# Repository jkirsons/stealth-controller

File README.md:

# Stealth Controller
A Field Oriented Control Brushless DC Motor Controller.

With 8A driver, Magnetic Sensor, Microcontroller, Two-Wire Automotive Interface

---
BOM

Ref | Qnty | Value | Size | LCSC #
--- | --- | --- | --- | --- 
C3, C21, C22, C23, C24, C25, C26, |7|22uF 25v|0805|[C45783](https://lcsc.com/product-detail/Multilayer-Ceramic-Capacitors-MLCC-SMD-SMT_Samsung-Electro-Mechanics-CL21A226MAQNNNE_C45783.html)
C1, C15, C16, |3|22uF 10v|0603|[C86295](https://lcsc.com/product-detail/Multilayer-Ceramic-Capacitors-MLCC-SMD-SMT_Samsung-Electro-Mechanics-CL10A226MP8NUNE_C86295.html)
C9, C18, C20, |3|10uF 10v|0603|[C19702](https://lcsc.com/product-detail/Multilayer-Ceramic-Capacitors-MLCC-SMD-SMT_Samsung-Electro-Mechanics-CL10A106KP8NNNC_C19702.html)
C11, |1|2.2uF 50v|0805|[C337444](https://lcsc.com/product-detail/Others_Taiyo-Yuden-UMK212ABJ225KG-T_C337444.html)
C4, C6, C10, C13, |4|1uF 16v|0603|[C318643](https://lcsc.com/product-detail/Multilayer-Ceramic-Capacitors-MLCC-SMD-SMT_Samsung-Electro-Mechanics-CL10A105KO5LNNC_C318643.html)
C2, C7, C8, C12, C14, C17, C19, |7|100nF 50v|0603|[C490602](https://lcsc.com/product-detail/Multilayer-Ceramic-Capacitors-MLCC-SMD-SMT_KEMET-C0603C104J5RAC_C490602.html)
C5, |1|10nF 50v|0603|[C128615](https://lcsc.com/product-detail/Multilayer-Ceramic-Capacitors-MLCC-SMD-SMT_Walsin-Tech-Corp-0603B103J500CT_C128615.html)
L1, |1|15uH|1210|[C478845](https://lcsc.com/product-detail/Inductors-SMD_Taiyo-Yuden-BRL3225T150K_C478845.html)
R1, |1|22|0603|[C269708](https://lcsc.com/product-detail/Chip-Resistor-Surface-Mount_TyoHM-RMC0603221-N_C269708.html)
R2|1|5.1k|0603|[C103696](https://lcsc.com/product-detail/Chip-Resistor-Surface-Mount_RALEC-RTT03512JTP_C103696.html)
R3, R4, |2|10K|0603|[C328335](https://lcsc.com/product-detail/Chip-Resistor-Surface-Mount_Resistor-Today-AECR0603F10K0K9_C328335.html)
R5, |1|120|0603|[C22787](https://lcsc.com/product-detail/Chip-Resistor-Surface-Mount_UNI-ROYAL-Uniroyal-Elec-0603WAF1200T5E_C22787.html)
IC1, |1|ESP32-PICO-V3|ESP32-PICO-V3|[C967022](https://lcsc.com/product-detail/RF-Transceiver-ICs_Espressif-Systems-ESP32-PICO-V3_C967022.html)
IC2, |1|LMR36506|LMR36506|[TI](https://www.ti.com/store/ti/en/p/product/?p=LMR36506R3RPER)
IC3, |1|MA702GQ-P|MA702GQ-P|[Mouser](https://www.mouser.ch/ProductDetail/Monolithic-Power-Systems-MPS/MA702GQ-P?qs=%2Fha2pyFadugcckvyIxaK%2FPg3fxrEo4S43%2FImNSAiLmAbp7VlBKN7pA%3D%3D)
IC4, |1|SN65HVD230QDRG4|SN65HVD230QDRG4|[C16468](https://lcsc.com/product-detail/CAN-ICs_Texas-Instruments-SN65HVD230QDR_C16468.html)
U1, |1|DRV8316R|DRV8316R|[TI](https://www.ti.com/product/DRV8316?keyMatch=DRV8316&tisearch=search-everything&usecase=GPN#order-quality)
Reset1, Boot1, |2|SW_Push_Dual|XKB Connectivity TS-1177-B-B-B|[C561510](https://lcsc.com/product-detail/Tactile-Switches_XKB-Connectivity-TS-1177-B-B-B_C561510.html)
UART1, TWAI1, TWAI2, |3|UART/TWAI|S3B-ZR-SM4A-TF|[C158001](https://lcsc.com/product-detail/Wire-To-Board-Wire-To-Wire-Connector_JST-Sales-America-B3B-ZR-LF-SN_C158001.html)
J1, |1|XT30PB|XT30PB|[C428721](https://lcsc.com/product-detail/Power-Connectors_Changzhou-Amass-Elec-XT30UPB-M_C428721.html)

---

Links:
[Simple FOC](https://simplefoc.com/)

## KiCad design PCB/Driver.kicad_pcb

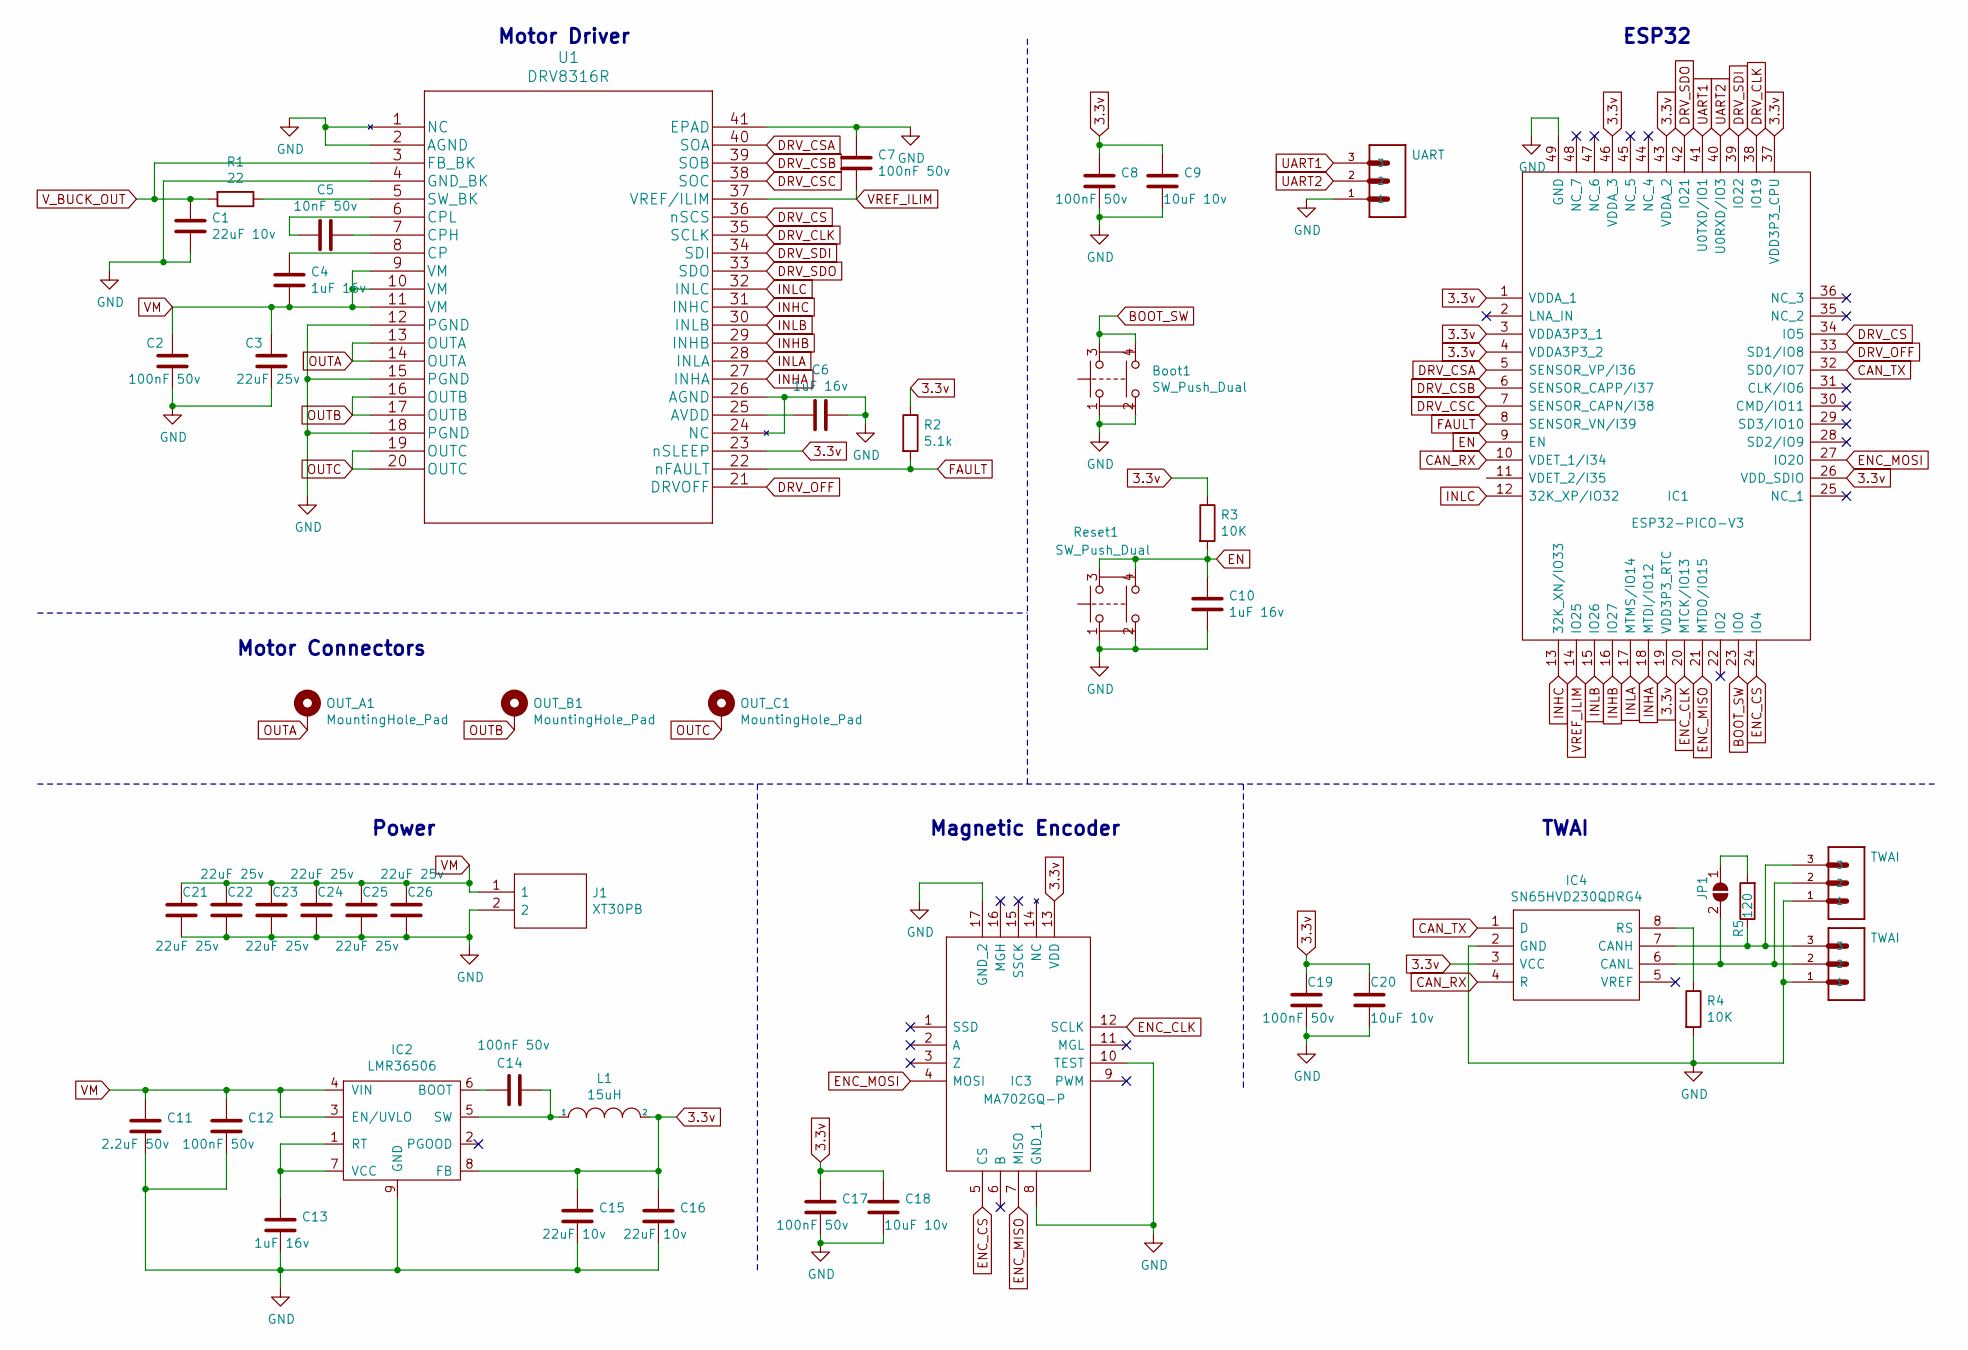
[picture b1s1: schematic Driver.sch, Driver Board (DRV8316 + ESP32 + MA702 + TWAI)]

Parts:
Boot1: SW_Push_Dual; XKB_Connectivity_TS-1177-B-B-B
C1, C15, C16: 22uF 10v; C_0603_1608Metric
C2, C7, C8, C12, C14, C17, C19: 100nF 50v; C_0603_1608Metric
C3, C21, C22, C23, C24, C25, C26: 22uF 25v; C_0805_2012Metric
C4, C6, C10, C13: 1uF 16v; C_0603_1608Metric
C5: 10nF 50v; C_0603_1608Metric
C9, C18, C20: 10uF 10v; C_0603_1608Metric
C11: 2.2uF 50v; C_0805_2012Metric
IC1: ESP32-PICO-V3; ESP32PICOV3; Manufacturer_Part_Number ESP32-PICO-V3; Mouser Part Number 356-ESP32-PICO-V3
IC2: LMR36506
IC3: MA702GQ-P; MA702; Manufacturer_Part_Number MA702GQ-P; Mouser Part Number 946-MA702GQ-P
IC4: SN65HVD230QDRG4; SN65HVD230QDR; Manufacturer_Part_Number SN65HVD230QDRG4; Mouser Part Number 595-SN65HVD230QDRG4
J1: XT30PB; Manufacturer_Part_Number XT30PB
JP1: SolderJumper_2_Open; SolderJumper-2_P1.3mm_Open_RoundedPad1.0x1.5mm
L1: 15uH; L_1210_3225Metric; MPN NLCV32T-470K-PF; LCSC C83083
OUT_A1: MountingHole_Pad; Motor_Wire_Solder_Pad
OUT_B1: MountingHole_Pad; Motor_Wire_Solder_Pad
OUT_C1: MountingHole_Pad; Motor_Wire_Solder_Pad
R1: 22; R_0603_1608Metric
R2: 5.1k; R_0603_1608Metric
R3, R4: 10K; R_0603_1608Metric
R5: 120; R_0603_1608Metric
Reset1: SW_Push_Dual; XKB_Connectivity_TS-1177-B-B-B
TWAI1, TWAI2: TWAI; SHDR3W50P0X150
U1: DRV8316R; DRV8316
UART1: UART; SHDR3W50P0X150

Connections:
3.3v: C8.1, C9.1, C15.1, C16.1, C17.1, C18.1, C19.1, C20.1, IC1.1 (VDDA_1), IC1.3 (VDDA3P3_1), IC1.4 (VDDA3P3_2), IC1.19 (VDD3P3_RTC), IC1.26 (VDD_SDIO), IC1.37 (VDD3P3_CPU), IC1.43 (VDDA_2), IC1.46 (VDDA_3), IC2.8 (FB), IC3.13 (VDD), IC4.3 (VCC), L1.2, R2.1, R3.1, U1.23 (nSLEEP)
BOOT_SW: Boot1.3, Boot1.4, IC1.23 (IO0)
CAN_RX: IC1.10 (VDET_1/I34), IC4.4 (R)
CAN_TX: IC1.32 (SD0/IO7), IC4.1 (D)
DRV_CLK: IC1.38 (IO19), U1.35 (SCLK)
DRV_CS: IC1.34 (IO5), U1.36 (nSCS)
DRV_CSA: IC1.5 (SENSOR_VP/I36), U1.40 (SOA)
DRV_CSB: IC1.6 (SENSOR_CAPP/I37), U1.39 (SOB)
DRV_CSC: IC1.7 (SENSOR_CAPN/I38), U1.38 (SOC)
DRV_OFF: IC1.33 (SD1/IO8), U1.21 (DRVOFF)
DRV_SDI: IC1.39 (IO22), U1.34 (SDI)
DRV_SDO: IC1.42 (IO21), U1.33 (SDO)
EN: C10.1, IC1.9 (EN), R3.2, Reset1.3, Reset1.4
ENC_CLK: IC1.20 (MTCK/IO13), IC3.12 (SCLK)
ENC_CS: IC1.24 (IO4), IC3.5 (CS)
ENC_MISO: IC1.21 (MTDO/IO15), IC3.7 (MISO)
ENC_MOSI: IC1.27 (IO20), IC3.4 (MOSI)
FAULT: IC1.8 (SENSOR_VN/I39), R2.2, U1.22 (nFAULT)
GND: Boot1.1, Boot1.2, C1.2, C2.2, C3.2, C6.1, C7.1, C8.2, C9.2, C10.2, C11.2, C12.2, C13.2, C15.2, C16.2, C17.2, C18.2, C19.2, C20.2, C21.2, C22.2, C23.2, C24.2, C25.2, C26.2, IC1.49 (GND), IC2.9 (GND), IC3.8 (GND_1), IC3.10 (TEST), IC3.17 (GND_2), IC4.2 (GND), J1.2, R4.2, Reset1.1, Reset1.2, TWAI1.1, TWAI2.1, U1.1 (NC), U1.2 (AGND), U1.4 (GND_BK), U1.12 (PGND), U1.15 (PGND), U1.18 (PGND), U1.24 (NC), U1.26 (AGND), U1.41 (EPAD), UART1.1; also elsewhere on the board
INHA: IC1.18 (MTDI/IO12), U1.27 (INHA)
INHB: IC1.16 (IO27), U1.29 (INHB)
INHC: IC1.13 (32K_XN/IO33), U1.31 (INHC)
INLA: IC1.17 (MTMS/IO14), U1.28 (INLA)
INLB: IC1.15 (IO26), U1.30 (INLB)
INLC: IC1.12 (32K_XP/IO32), U1.32 (INLC)
unnamed: C4.1, U1.8 (CP)
unnamed: C5.1, U1.7 (CPH)
unnamed: C5.2, U1.6 (CPL)
unnamed: C6.2, U1.25 (AVDD)
unnamed: C13.1, IC2.1 (RT), IC2.7 (VCC)
unnamed: C14.1, IC2.6 (BOOT)
unnamed: C14.2, IC2.5 (SW), L1.1
unnamed 32: IC4.6 (CANL), JP1.2 (B), TWAI1.2, TWAI2.2; also elsewhere on the board
unnamed 33: IC4.7 (CANH), R5.1, TWAI1.3, TWAI2.3; also elsewhere on the board
unnamed: IC4.8 (RS), R4.1
unnamed: JP1.1 (A), R5.2
unnamed: R1.1, U1.5 (SW_BK)
OUTA: OUT_A1.1, U1.13 (OUTA), U1.14 (OUTA)
OUTB: OUT_B1.1, U1.16 (OUTB), U1.17 (OUTB)
OUTC: OUT_C1.1, U1.19 (OUTC), U1.20 (OUTC)
UART1: IC1.41 (U0TXD/IO1), UART1.3
UART2: IC1.40 (U0RXD/IO3), UART1.2
VM: C2.1, C3.1, C4.2, C11.1, C12.1, C21.1, C22.1, C23.1, C24.1, C25.1, C26.1, IC2.3 (EN/UVLO), IC2.4 (VIN), J1.1, U1.9 (VM), U1.10 (VM), U1.11 (VM)
VREF_ILIM: C7.2, IC1.14 (IO25), U1.37 (VREF/ILIM)
V_BUCK_OUT: C1.1, R1.2, U1.3 (FB_BK)

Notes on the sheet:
Motor Driver
Motor Connectors
ESP32
Magnetic Encoder
TWAI
Power

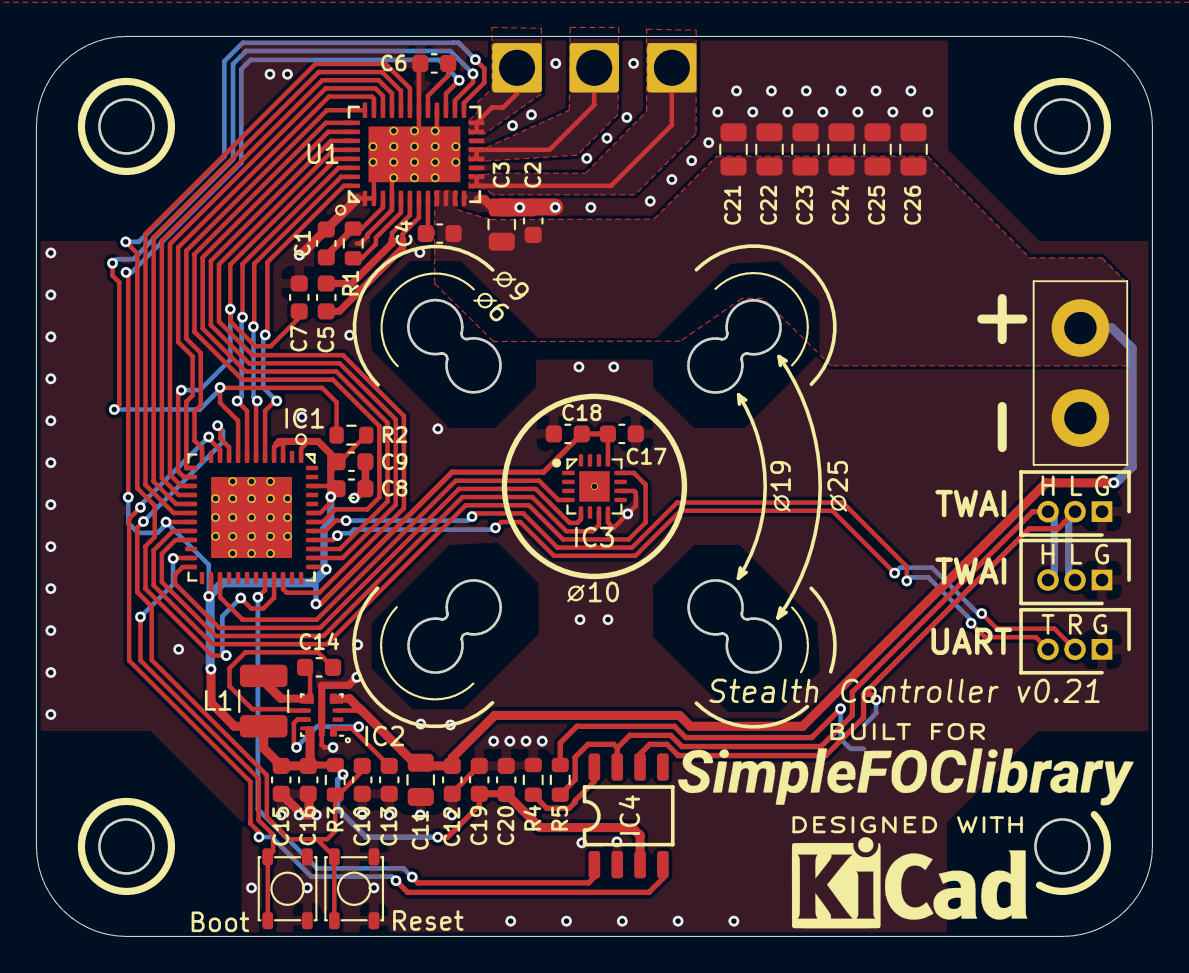
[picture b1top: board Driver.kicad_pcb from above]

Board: 2 copper layers, 62.0 x 50.0 mm, 47 parts (1 on the bottom side), 45 nets.

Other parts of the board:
CAN1, CAN2: CAN; SHDR3W50P0X150

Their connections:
GND: CAN1.1, CAN2.1; also elsewhere on the board
unnamed 32: CAN1.2, CAN2.2; also elsewhere on the board
unnamed 33: CAN1.3, CAN2.3; also elsewhere on the board

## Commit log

2021-05-02 add image
2021-05-02 change readme
2021-05-06 Added part links
2021-05-12 can framework
2021-05-17 CAN interface - receiving
2021-05-17 can restructure
2021-05-19 CAN update - capture commander output
2021-05-20 Rename CAN files to match classes
2021-05-21 cleanup
2021-05-26 Update CAN driver - Bus ID + ROS2 example
2021-05-28 Move CAN to library, Stealth controller functions to local library
2021-05-28 Pin definitions
2021-05-28 update main
2021-05-31 Update - CAN HAT
2021-05-31 New Line
2021-05-31 move ROS2 to folder
2021-05-31 Update Tasks
2021-05-31 Windows Tasks
2021-06-03 ROS Updates
2021-06-04 Windows Env
2021-06-04 reverse commands
2021-06-04 handler

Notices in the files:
PCB/Driver.sch:
MIT License
